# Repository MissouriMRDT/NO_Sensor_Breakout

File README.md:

# NO_Sensor_Breakout
Breakout board for the USEQGSEAN8L180 NO Sensor

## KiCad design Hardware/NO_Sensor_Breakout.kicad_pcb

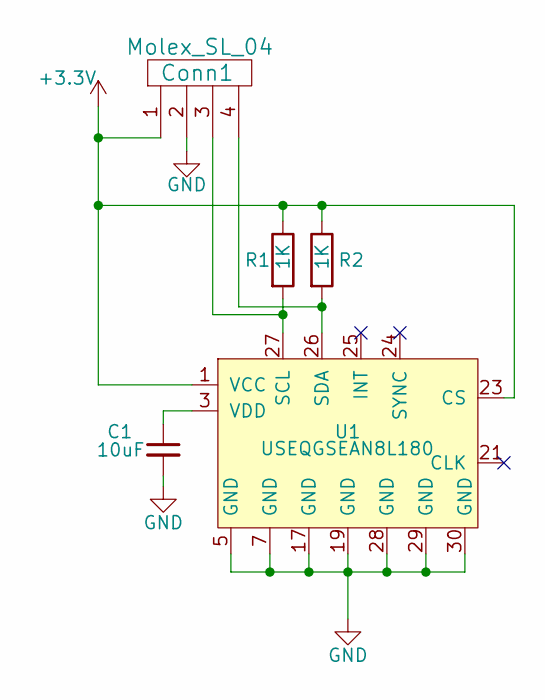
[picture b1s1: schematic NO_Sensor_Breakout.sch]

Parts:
C1: 10uF; C_0603_1608Metric_Pad1.08x0.95mm_HandSolder
Conn1: Molex_SL_04; MOLEX_SL_04_Vertical
R1, R2: 1K; R_0603_1608Metric_Pad0.98x0.95mm_HandSolder
U1: USEQGSEAN8L180

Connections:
+3V3: Conn1.1, R1.1, R2.1, U1.1 (VCC), U1.23 (CS)
GND: C1.2, Conn1.2, U1.5 (GND), U1.7 (GND), U1.17 (GND), U1.19 (GND), U1.28 (GND), U1.29 (GND), U1.30 (GND)
unnamed: C1.1, U1.3 (VDD)
unnamed: Conn1.3, R1.2, U1.27 (SCL)
unnamed: Conn1.4, R2.2, U1.26 (SDA)

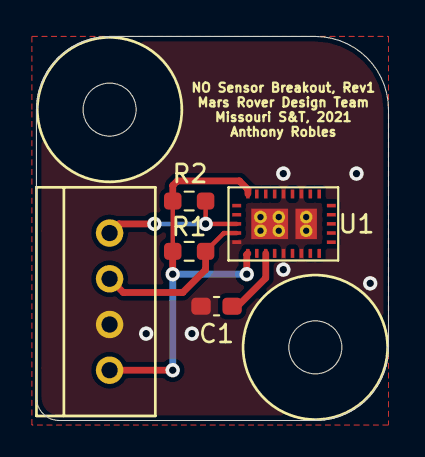
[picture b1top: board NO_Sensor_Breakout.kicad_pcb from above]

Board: 2 copper layers, 19.6 x 21.3 mm, 5 parts (0 on the bottom side), 5 nets.

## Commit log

2020-11-28 Created Master
2020-11-28 First Rev of NO Sensor Breakout
2020-11-28 Finished BOM
2020-11-28 Cleaned up schematic
